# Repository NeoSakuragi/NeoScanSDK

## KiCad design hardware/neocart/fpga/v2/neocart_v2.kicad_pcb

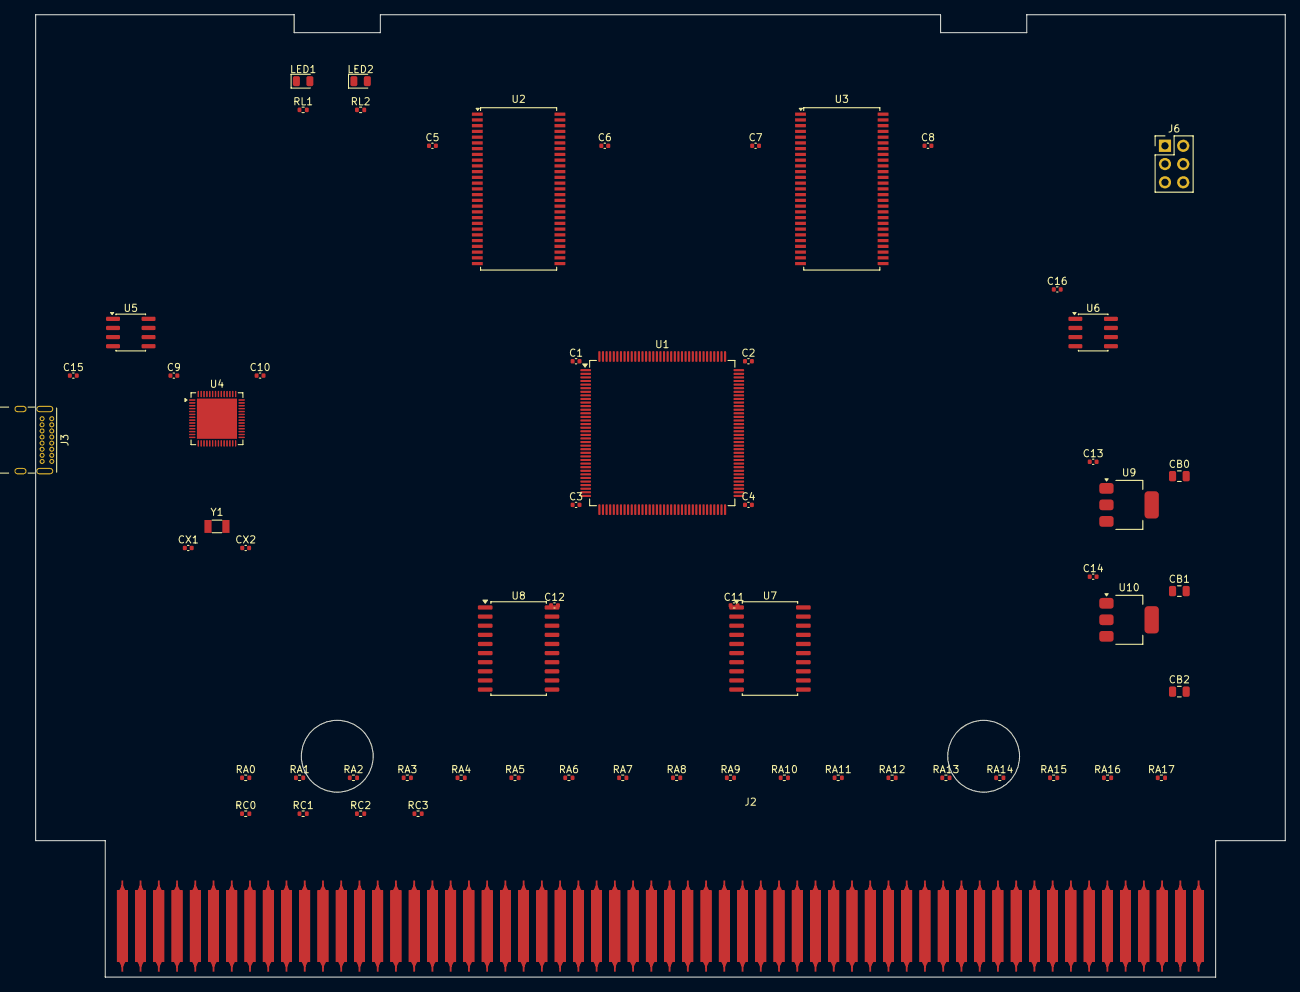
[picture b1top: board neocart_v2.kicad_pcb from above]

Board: 4 copper layers, 174.0 x 134.0 mm, 62 parts (0 on the bottom side), 102 nets, no tracks yet.

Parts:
C1, C2, C3, C4, C5, C6, C7, C8, C9, C10, C11, C12, C13, C14, C15, C16: 100n; C_0402_1005Metric
CB0, CB1, CB2: 10u; C_0805_2012Metric
CX1, CX2: 15p; C_0402_1005Metric
J1: CTRG2-B; neogeo-mvs-prog-b-side-edge
J2: CTRG2-A; neogeo-mvs-prog-a-side-edge
J3: USB; USB_C_Receptacle_GCT_USB4085
J6: JTAG; PinHeader_2x03_P2.54mm_Vertical
LED1: PWR; LED_0805_2012Metric
LED2: ACT; LED_0805_2012Metric
RA0, RA1, RA2, RA3, RA4, RA5, RA6, RA7, RA8, RA9, RA10, RA11, RA12, RA13, RA14, RA15, RA16, RA17: 470; R_0402_1005Metric
RC0, RC1, RC2, RC3: 470; R_0402_1005Metric
RL1, RL2: 1K; R_0402_1005Metric
U1: ECP5; TQFP-144_20x20mm_P0.5mm
U2: SDRAM1; TSOP-II-54_22.2x10.16mm_P0.8mm
U3: SDRAM2; TSOP-II-54_22.2x10.16mm_P0.8mm
U4: RP2040; QFN-56-1EP_7x7mm_P0.4mm_EP5.6x5.6mm
U5: FL-MCU; SOIC-8_3.9x4.9mm_P1.27mm
U6: FL-CFG; SOIC-8_3.9x4.9mm_P1.27mm
U7: 245-LO; SOIC-20W_7.5x12.8mm_P1.27mm
U8: 245-HI; SOIC-20W_7.5x12.8mm_P1.27mm
U9: 3V3; SOT-223-3_TabPin2
U10: 1V1; SOT-223-3_TabPin2
Y1: 12M; Crystal_SMD_3215-2Pin_3.2x1.5mm

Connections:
BUF_OE: U1.33, U7.19, U8.19
BUS_DIR: U1.31, U7.1, U8.1
FD0: U1.37, U7.18
FD1: U1.39, U7.17
FD2: U1.40, U7.16
FD3: U1.41, U7.15
FD4: U1.44, U7.14
FD5: U1.45, U7.13
FD6: U1.46, U7.12
FD7: U1.47, U7.11
FD8: U1.48, U8.18
FD9: U1.49, U8.17
FD10: U1.50, U8.16
FD11: U1.51, U8.15
FD12: U1.52, U8.14
FD13: U1.67, U8.13
FD14: U1.68, U8.12
FD15: U1.69, U8.11
GND: C1.2, C2.2, C3.2, C4.2, C5.2, C6.2, C7.2, C8.2, C9.2, C10.2, C11.2, C12.2, C13.2, C14.2, C15.2, C16.2, CB0.2, CB1.2, CB2.2, CX1.2, CX2.2, J1.1, J1.2, J1.3, J1.4, J1.59, J1.60, J2.1, J2.2, J2.3, J2.4, J2.59, J2.60, LED1.2, LED2.2, U1.15, U1.21, U1.36, U1.42, U1.54, U1.57, U1.60, U1.63, U1.66, U1.75, U1.87, U1.96, U1.123, U1.129, U1.132, U1.138, U1.144, U2.6, U2.12, U2.28, U2.40, U2.41, U2.46, U2.52, U2.54, U3.6, U3.12, U3.28, U3.40, U3.41, U3.46, U3.52, U3.54, U7.10, U8.10, U9.1, U10.1
LED1: LED1.1, RL1.1, RL1.2, U1.34
LED2: LED2.1, RL2.1, RL2.2, U1.35
PA0: J1.5, RA0.1, RA0.2, U1.1
PA1: J1.6, RA1.1, RA1.2, U1.2
PA2: J1.7, RA2.1, RA2.2, U1.3
PA3: J1.8, RA3.1, RA3.2, U1.4
PA4: J1.9, RA4.1, RA4.2, U1.5
PA5: J1.10, RA5.1, RA5.2, U1.6
PA6: J1.11, RA6.1, RA6.2, U1.7
PA7: J1.12, RA7.1, RA7.2, U1.10
PA8: J1.13, RA8.1, RA8.2, U1.11
PA9: J1.14, RA9.1, RA9.2, U1.12
PA10: J1.15, RA10.1, RA10.2, U1.13
PA11: J1.16, RA11.1, RA11.2, U1.14
PA12: J1.17, RA12.1, RA12.2, U1.18
PA13: J1.18, RA13.1, RA13.2, U1.19
PA14: J1.19, RA14.1, RA14.2, U1.22
PA15: J1.20, RA15.1, RA15.2, U1.23
PA16: J1.21, RA16.1, RA16.2, U1.24
PA17: J1.22, RA17.1, RA17.2, U1.25
PD0: J2.5, U7.2
PD1: J2.6, U7.3
PD2: J2.7, U7.4
PD3: J2.8, U7.5
PD4: J2.9, U7.6
PD5: J2.10, U7.7
PD6: J2.11, U7.8
PD7: J2.12, U7.9
PD8: J2.13, U8.2
PD9: J2.14, U8.3
PD10: J2.15, U8.4
PD11: J2.16, U8.5
PD12: J2.17, U8.6
PD13: J2.18, U8.7
PD14: J2.19, U8.8
PD15: J2.20, U8.9
ROMOE: J2.33, RC0.1, RC0.2, U1.26
ROMOEL: J2.24, RC2.1, RC2.2, U1.28
ROMOEU: J2.23, RC1.1, RC1.2, U1.27
SD_A0: U1.94, U2.23, U3.23
SD_A1: U1.95, U2.24, U3.24
SD_A2: U1.97, U2.25, U3.25
SD_A3: U1.98, U2.26, U3.26
SD_A4: U1.99, U2.29, U3.29
SD_A5: U1.102, U2.30, U3.30
SD_A6: U1.103, U2.31, U3.31
SD_A7: U1.104, U2.32, U3.32
SD_A8: U1.105, U2.33, U3.33
SD_A9: U1.106, U2.34, U3.34
SD_A10: U1.107, U2.22, U3.22
SD_A11: U1.108, U2.35, U3.35
SD_A12: U1.110, U2.36, U3.36
SD_BA0: U1.111, U2.20, U3.20
SD_BA1: U1.112, U2.21, U3.21
SD_CAS: U1.116, U2.17, U3.17
SD_CKE: U1.114, U2.37, U3.37
SD_CLK: U1.113, U2.38, U3.38
SD_CS0: U1.118, U2.19
SD_CS1: U1.119, U3.19
SD_DQ0: U1.73, U2.2, U3.2
SD_DQ1: U1.74, U2.4, U3.4
SD_DQ2: U1.76, U2.5, U3.5
SD_DQ3: U1.77, U2.7, U3.7
SD_DQ4: U1.78, U2.8, U3.8
SD_DQ5: U1.79, U2.10, U3.10
SD_DQ6: U1.80, U2.11, U3.11
SD_DQ7: U1.81, U2.13, U3.13
SD_DQ8: U1.82, U2.42, U3.42
SD_DQ9: U1.84, U2.44, U3.44
SD_DQ10: U1.88, U2.45, U3.45
SD_DQ11: U1.89, U2.47, U3.47
SD_DQ12: U1.90, U2.48, U3.48
SD_DQ13: U1.91, U2.50, U3.50
SD_DQ14: U1.92, U2.51, U3.51
SD_DQ15: U1.93, U2.53, U3.53
SD_DQMH: U1.121, U2.39, U3.39
SD_DQML: U1.120, U2.15, U3.15
SD_RAS: U1.115, U2.18, U3.18
SD_WE: U1.117, U2.16, U3.16
VCC_1V1: U1.16, U1.43, U1.55, U1.58, U1.61, U1.64, U1.70, U1.85, U1.100, U1.109, U1.130, U10.2
VCC_3V3: C1.1, C2.1, C3.1, C4.1, C5.1, C6.1, C7.1, C8.1, C9.1, C10.1, C11.1, C12.1, C13.1, C14.1, C15.1, C16.1, CB0.1, CB1.1, CB2.1, CX1.1, CX2.1, U1.8, U1.17, U1.20, U1.29, U1.32, U1.38, U1.53, U1.56, U1.59, U1.62, U1.65, U1.83, U1.86, U1.101, U1.122, U1.131, U1.137, U2.1, U2.3, U2.9, U2.14, U2.27, U2.43, U2.49, U3.1, U3.3, U3.9, U3.14, U3.27, U3.43, U3.49, U9.2, U10.3
VCC_5V: J1.29, J1.30, J1.31, J1.32, J2.29, J2.30, J2.31, J2.32, U7.20, U8.20, U9.3
nRW: J2.21, RC3.1, RC3.2, U1.30

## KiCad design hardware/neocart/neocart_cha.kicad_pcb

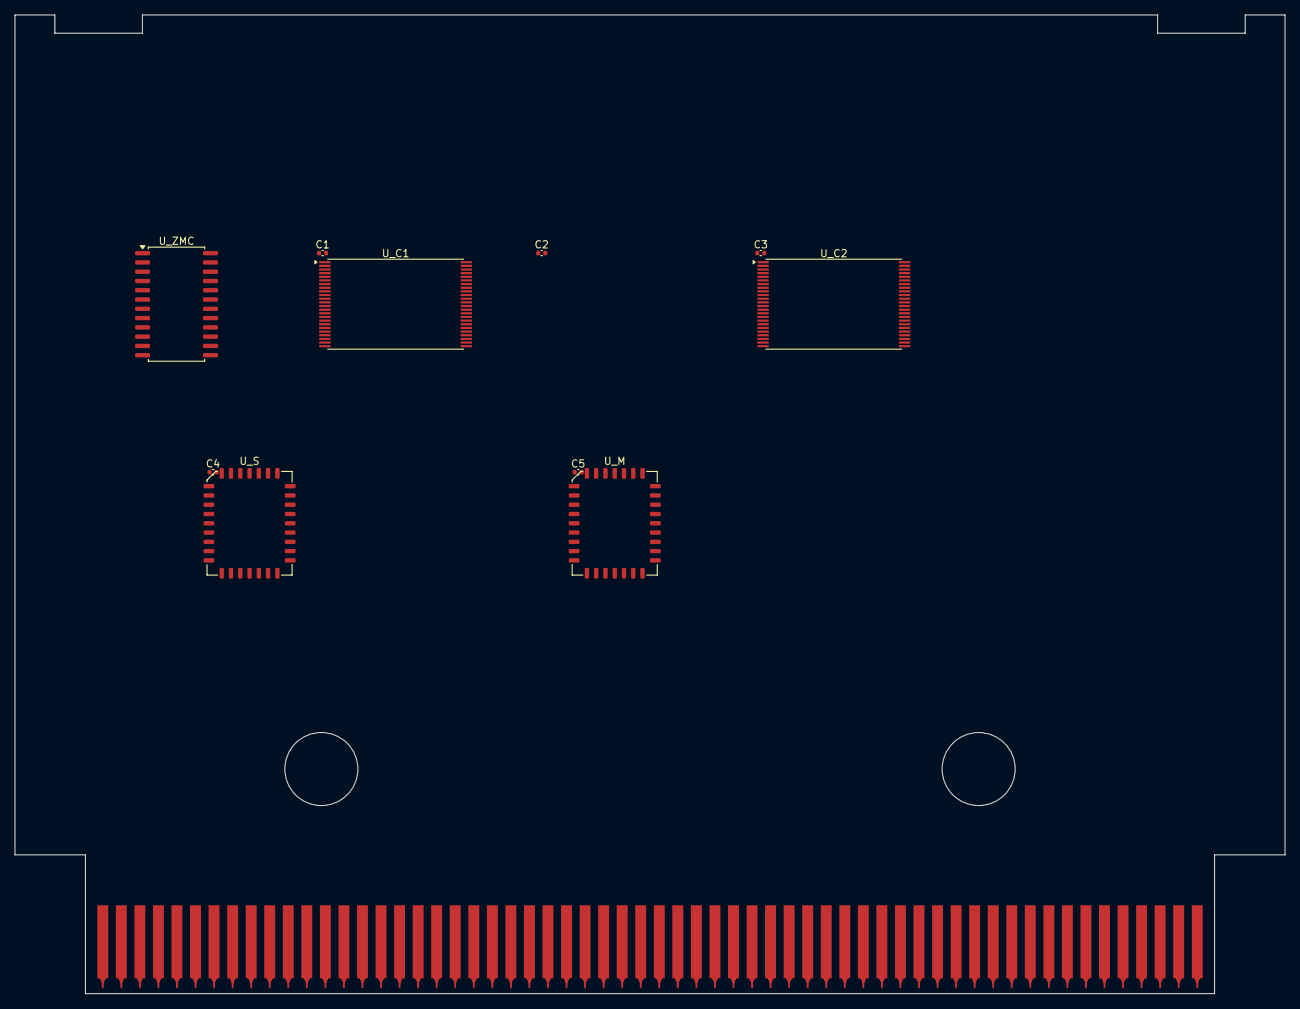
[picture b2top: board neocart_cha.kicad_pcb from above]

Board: 4 copper layers, 173.9 x 134.0 mm, 12 parts (1 on the bottom side), 2 nets, no tracks yet.

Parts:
C1, C2, C3, C4, C5: 100nF; C_0402_1005Metric
J1: neogeo-mvs-cha-a-side-edge; neogeo-mvs-a-side-edge
J4: neogeo-mvs-cha-b-side-edge; neogeo-mvs-b-side-edge
U_C1: AM29F400_C1; TSOP-I-48_18.4x12mm_P0.5mm
U_C2: AM29F400_C2; TSOP-I-48_18.4x12mm_P0.5mm
U_M: SST39SF010_M; PLCC-32_11.4x14.0mm_P1.27mm
U_S: SST39SF010_S; PLCC-32_11.4x14.0mm_P1.27mm
U_ZMC: NEO-ZMC; SOIC-24W_7.5x15.4mm_P1.27mm

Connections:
GND: J1.1 (GND), J1.2 (GND), J1.59 (GND), J1.60 (GND), J4.1 (GND), J4.2 (GND), J4.59 (GND), J4.60 (GND)
VCC: J1.29 (VCC), J1.30 (VCC), J1.31 (VCC), J1.32 (VCC), J4.29 (VCC), J4.30 (VCC), J4.31 (VCC), J4.32 (VCC)

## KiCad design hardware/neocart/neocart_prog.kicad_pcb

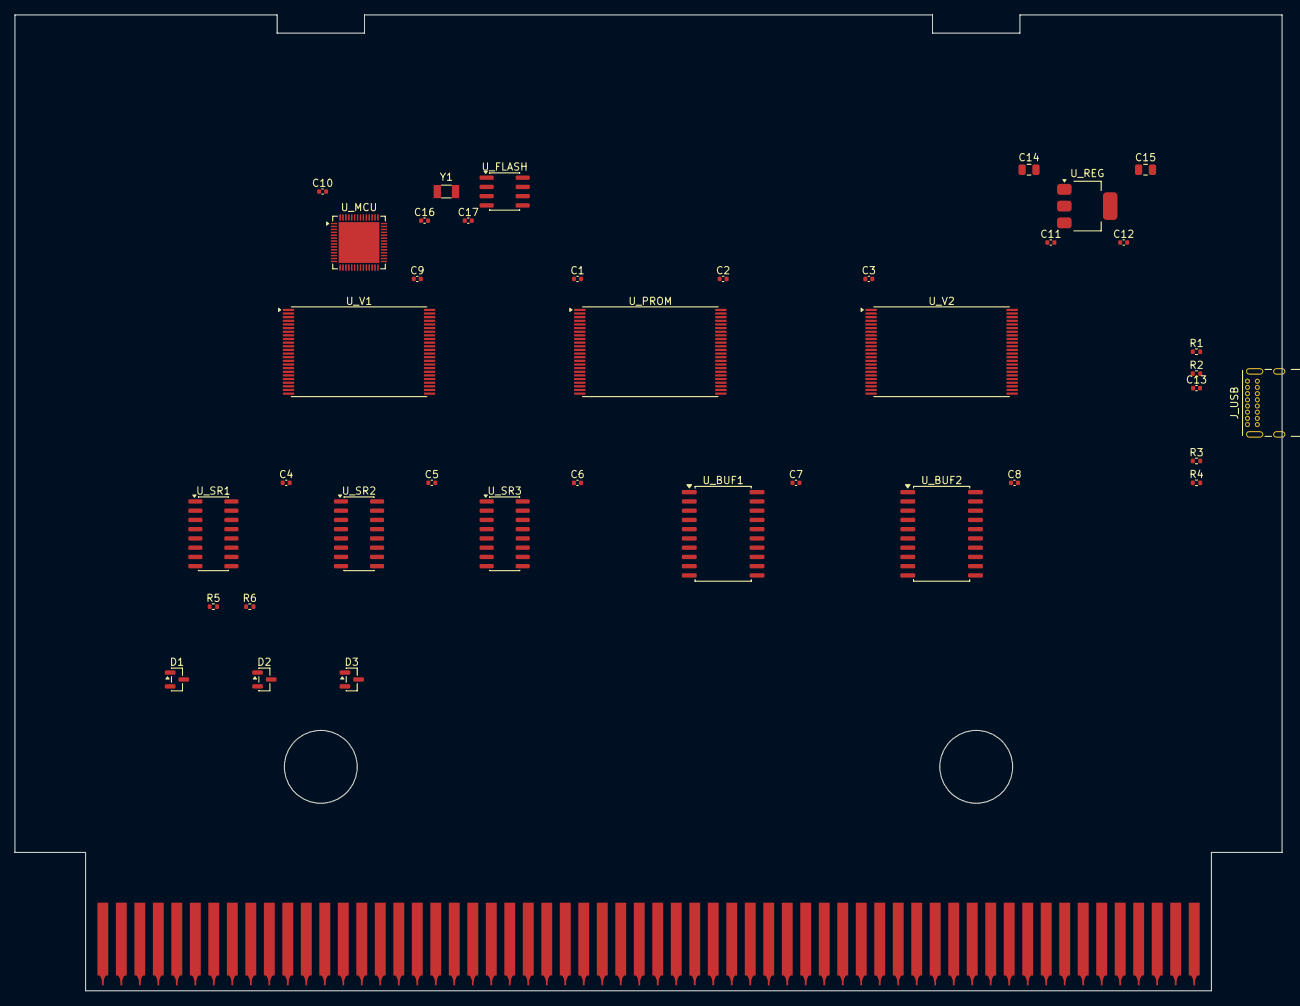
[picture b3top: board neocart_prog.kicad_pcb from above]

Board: 4 copper layers, 174.0 x 134.0 mm, 41 parts (1 on the bottom side), 2 nets, no tracks yet.

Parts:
C1, C2, C3, C4, C5, C6, C7, C8, C9, C10, C11, C12, C13: 100nF; C_0402_1005Metric
C14, C15: 10uF; C_0805_2012Metric
C16, C17: 15pF; C_0402_1005Metric
D1, D2, D3: BAT54S; SOT-23
J1: NeoGeo MVS Prog B Side Edge; neogeo-mvs-prog-b-side-edge
J2: NeoGeo MVS Prog A Side Edge; neogeo-mvs-prog-a-side-edge
J_USB: USB_C; USB_C_Receptacle_GCT_USB4085
R1, R2: 27R; R_0402_1005Metric
R3, R4: 5.1K; R_0402_1005Metric
R5, R6: 10K; R_0402_1005Metric
U_BUF1: 74HC245_DATA; SOIC-20W_7.5x12.8mm_P1.27mm
U_BUF2: 74HC245_CTRL; SOIC-20W_7.5x12.8mm_P1.27mm
U_FLASH: W25Q32; SOIC-8_3.9x4.9mm_P1.27mm
U_MCU: RP2040; QFN-56-1EP_7x7mm_P0.4mm_EP5.6x5.6mm
U_PROM: AM29F400_P; TSOP-I-48_18.4x12mm_P0.5mm
U_REG: AMS1117-3.3; SOT-223-3_TabPin2
U_SR1, U_SR2, U_SR3: 74HC595; SOIC-16_3.9x9.9mm_P1.27mm
U_V1: AM29F400_V1; TSOP-I-48_18.4x12mm_P0.5mm
U_V2: AM29F400_V2; TSOP-I-48_18.4x12mm_P0.5mm
Y1: 12MHz; Crystal_SMD_3215-2Pin_3.2x1.5mm

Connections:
GND: J1.1 (GND), J1.2 (GND), J1.3 (GND), J1.4 (GND), J1.57 (GND), J1.58 (GND), J1.59 (GND), J1.60 (GND), J2.1 (GND), J2.2 (GND), J2.3 (GND), J2.4 (GND), J2.57 (GND), J2.58 (GND), J2.59 (GND), J2.60 (GND)
VCC: J1.25 (ROMWAIT), J1.26 (PWAIT0), J1.27 (PWAIT1), J1.28 (PDTACK), J1.29 (VCC), J1.30 (VCC), J1.31 (VCC), J1.32 (VCC), J2.29 (VCC), J2.30 (VCC), J2.31 (VCC), J2.32 (VCC)

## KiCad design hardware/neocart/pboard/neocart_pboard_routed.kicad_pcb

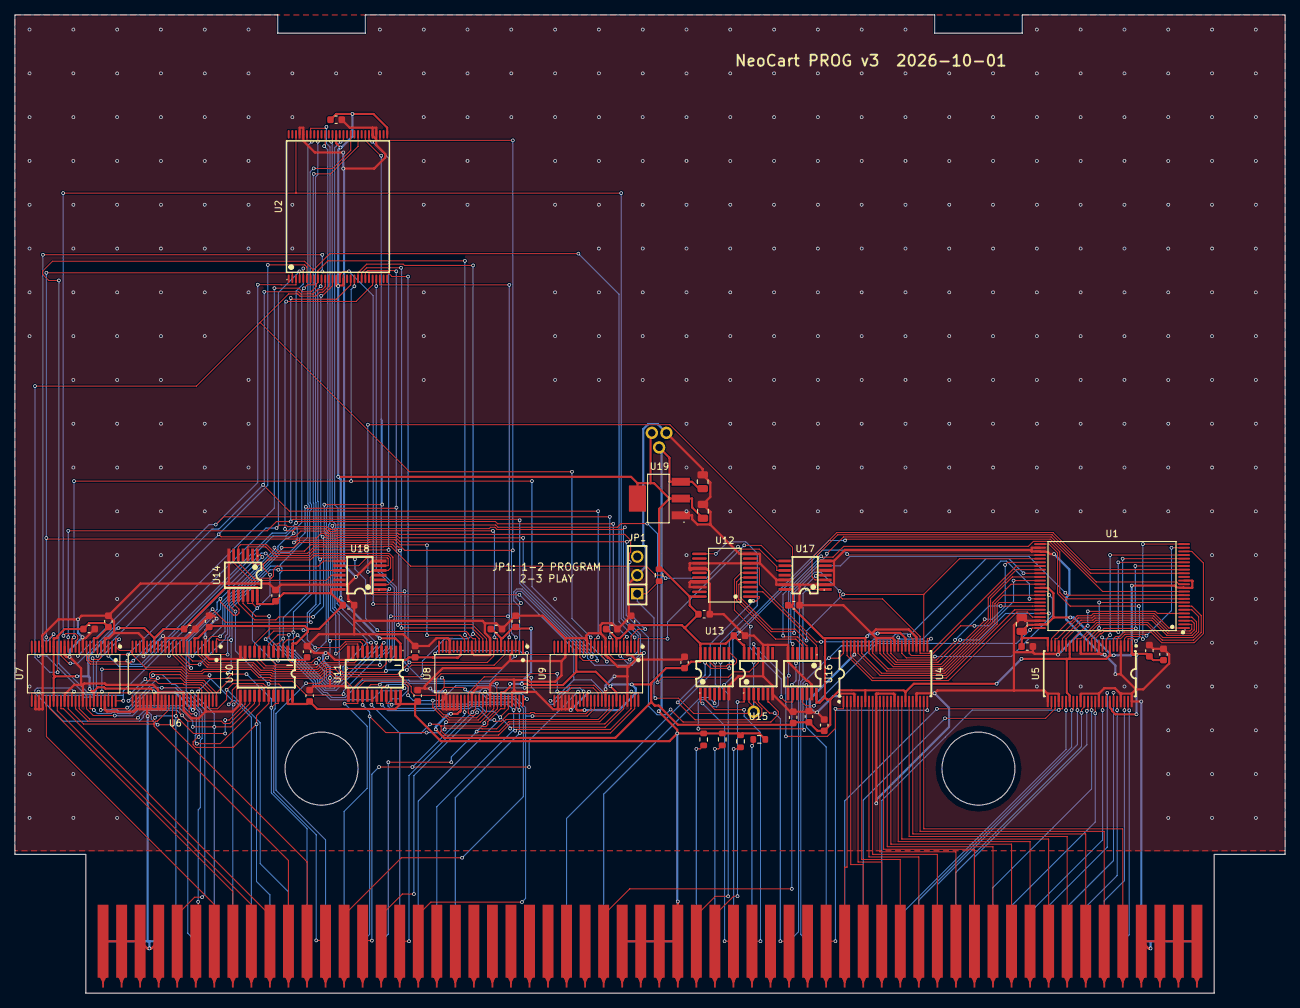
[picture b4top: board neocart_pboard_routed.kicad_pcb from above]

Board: 2 copper layers, 174.0 x 134.0 mm, 58 parts (1 on the bottom side), 172 nets.

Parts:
C1, C2, C3: 10u; C_0805_2012Metric
C4, C5, C6, C7, C8, C9, C10, C11, C12, C13, C14, C15, C16, C17, C18, C19, C20, C21, C22, C23, C24, C25, C26, C27, C28: 100n; C_0603_1608Metric
J1: NeoGeo MVS Prog B Side Edge; neogeo-mvs-prog-b-side-edge
J2: NeoGeo MVS Prog A Side Edge; neogeo-mvs-prog-a-side-edge
JP1: MODE; HDR-TH_03P-P2.54-V-M
R1, R2, R3, R4, R5: 10k; R_0603_1608Metric
TP1: GND; TP_PTH_1.0
TP2: P3V3; TP_PTH_1.0
TP3: VCC5; TP_PTH_1.0
TP4: nPROG; TP_PTH_1.0
U1: S29GL064N; TSOP-48_L12.0-W18.4-P0.50-LS20.0-BL
U2: S29GL128P; TSOP-56_L18.4-W14.0-P0.50-LS20.0-TL
U4, U5: SN74LVC16245A; TSSOP-48_L12.5-W6.1-P0.50-LS8.1-BL
U6, U7, U8, U9: 74LVC16374A; TSSOP-48_L12.6-W6.2-P0.50-LS8.1-BL
U10, U11: 74LVC8T245; TSSOP-24_L7.8-W4.4-P0.65-LS6.4-BL
U12: SN74AHC273; SSOP-20_L7.5-W5.2-P0.65-LS8.0-BL
U13, U14: SN74LVC08A; TSSOP-14_L5.0-W4.4-P0.65-LS6.4-BL
U15, U16, U17: 74LVC32A; TSSOP-14_L5.0-W4.4-P0.65-LS6.4-BL
U18: SN74LVC04A; TSSOP-14_L5.0-W4.4-P0.65-LS6.4-BL
U19: AMS1117-3.3; SOT-223-3_L6.5-W3.4-P2.30-LS7.0-BR

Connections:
A1: J1.5 (A1), U5.47
A2: J1.6 (A2), U5.46
A3: J1.7 (A3), U5.44
A4: J1.8 (A4), U5.43
A5: J1.9 (A5), U5.41
A6: J1.10 (A6), U5.40
A7: J1.11 (A7), U5.38
A8: J1.12 (A8), U5.37
A9: J1.13 (A9), U5.36
A10: J1.14 (A10), U5.35
A11: J1.15 (A11), U5.33
A12: J1.16 (A12), U5.32
A13: J1.17 (A13), U5.30
A14: J1.18 (A14), U5.29
A15: J1.19 (A15), U5.27
A16: J1.20 (A16), U5.26
A17: J1.21 (A17), U16.12
A18: J1.22 (A18), U17.1
A19: J1.23 (A19), U17.4
BANK0: U12.2, U16.1
BANK1: U12.5, U16.4
BANK2: U12.6, U16.9
D0: J2.5 (D0), U4.23
D1: J2.6 (D1), U4.22
D2: J2.7 (D2), U4.20
D3: J2.8 (D3), U4.19
D4: J2.9 (D4), U4.17
D5: J2.10 (D5), U4.16
D6: J2.11 (D6), U4.14
D7: J2.12 (D7), U4.13
D8: J2.13 (D8), U4.12
D9: J2.14 (D9), U4.11
D10: J2.15 (D10), U4.9
D11: J2.16 (D11), U4.8
D12: J2.17 (D12), U4.6
D13: J2.18 (D13), U4.5
D14: J2.19 (D14), U4.3
D15: J2.20 (D15), U4.2
FA0: U1.25, U5.2
FA1: U1.24, U5.3
FA2: U1.23, U5.5
FA3: U1.22, U5.6
FA4: U1.21, U5.8
FA5: U1.20, U5.9
FA6: U1.19, U5.11
FA7: U1.18, U5.12
FA8: U1.8, U5.13
FA9: U1.7, U5.14
FA10: U1.6, U5.16
FA11: U1.5, U5.17
FA12: U1.4, U5.19
FA13: U1.3, U5.20
FA14: U1.2, U5.22
FA15: U1.1, U5.23
FA16: U1.48, U16.11
FA17: U1.17, U17.3
FA18: U1.16, U17.6
FA19: U1.9, U16.3
FA20: U1.10, U16.6
FA21: U1.13, U16.8
FD0: U1.29, U4.26, U12.3
FD1: U1.31, U4.27, U12.4
FD2: U1.33, U4.29, U12.7
FD3: U1.35, U4.30
FD4: U1.38, U4.32
FD5: U1.40, U4.33
FD6: U1.42, U4.35
FD7: U1.44, U4.36
FD8: U1.30, U4.37
FD9: U1.32, U4.38
FD10: U1.34, U4.40
FD11: U1.36, U4.41
FD12: U1.39, U4.43
FD13: U1.41, U4.44
FD14: U1.43, U4.46
FD15: U1.45, U4.47
GND: C1.2, C2.2, C3.2, C4.2, C5.2, C6.2, C7.2, C8.2, C9.2, C10.2, C11.2, C12.2, C13.2, C14.2, C15.2, C16.2, C17.2, C18.2, C19.2, C20.2, C21.2, C22.2, C23.2, C24.2, C25.2, C26.2, C27.2, C28.2, J1.1 (GND), J1.2 (GND), J1.3 (GND), J1.4 (GND), J1.57 (GND), J1.58 (GND), J1.59 (GND), J1.60 (GND), J2.1 (GND), J2.2 (GND), J2.3 (GND), J2.4 (GND), J2.57 (GND), J2.58 (GND), J2.59 (GND), J2.60 (GND), JP1.2, TP1.1, U1.26, U1.27, U1.46, U2.32, U2.33, U2.52, U2.53, U4.4, U4.10, U4.15, U4.21, U4.28, U4.34, U4.39, U4.45, U5.4, U5.10, U5.15, U5.21, U5.25, U5.28, U5.34, U5.39, U5.45, U5.48, U6.4, U6.10, U6.15, U6.21, U6.26, U6.27, U6.28, U6.29, U6.30, U6.32, U6.33, U6.34, U6.39, U6.45, U7.4, U7.10, U7.15, U7.21, U7.26, U7.27, U7.28, U7.34, U7.39, U7.45, U8.4, U8.10, U8.15, U8.21, U8.26, U8.27, U8.28, U8.29, U8.30, U8.34, U8.39, U8.45, U9.4, U9.10, U9.15, U9.21, U9.26, U9.27, U9.28, U9.29, U9.30, U9.34, U9.39, U9.45, U10.11, U10.12, U10.13, U11.11, U11.12, U11.13, U12.8, U12.10, U12.13, U12.14, U12.17, U12.18, U13.7, U14.7, U15.7, U15.9, U15.10, U16.7, U16.13, U17.2, U17.5, U17.7, U17.12, U17.13, U18.7, U18.13, U19.1
P3V3: C2.1, C3.1, C4.1, C5.1, C6.1, C7.1, C8.1, C9.1, C10.1, C11.1, C12.1, C13.1, C14.1, C15.1, C16.1, C17.1, C18.1, C19.1, C20.1, C21.1, C22.1, C23.1, C24.1, C25.1, C27.1, R1.2, TP2.1, U1.12, U1.14, U1.37, U1.47, U2.14, U2.16, U2.29, U2.43, U4.7, U4.18, U4.31, U4.42, U5.1, U5.7, U5.18, U5.24, U5.31, U5.42, U6.7, U6.18, U6.31, U6.42, U7.7, U7.18, U7.31, U7.42, U8.7, U8.18, U8.31, U8.42, U9.7, U9.18, U9.31, U9.42, U10.1, U11.1, U11.2, U12.20, U13.14, U14.14, U15.14, U16.14, U17.14, U18.14, U19.2, U19.4
PDLY: U14.5, U17.10, U18.8
RW: J2.21 (R/W), U4.1, U4.24, U15.12
SDPA8: J2.43 (SDPA8), U8.36, U9.36
SDPA9: J2.44 (SDPA9), U8.35, U9.35
SDPA10: J2.45 (SDPA10), U8.33, U9.33
SDPA11: J2.46 (SDPA11), U8.32, U9.32
SDPAD0: J1.41 (SDPAD0), U8.47, U9.47, U11.21
SDPAD1: J1.42 (SDPAD1), U8.46, U9.46, U11.20
SDPAD2: J1.43 (SDPAD2), U8.44, U9.44, U11.19
SDPAD3: J1.44 (SDPAD3), U8.43, U9.43, U11.18
SDPAD4: J1.45 (SDPAD4), U8.41, U9.41, U11.17
SDPAD5: J1.46 (SDPAD5), U8.40, U9.40, U11.16
SDPAD6: J1.47 (SDPAD6), U8.38, U9.38, U11.15
SDPAD7: J1.48 (SDPAD7), U8.37, U9.37, U11.14
SDPMPX: J2.47 (SDPMPX), U8.25, U8.48, U18.3
SDPOE_I: U18.6, U18.9
SDRA8: J2.49 (SDRA8), U6.36, U7.36
SDRA9: J2.50 (SDRA9), U6.35, U7.35
SDRA20: J2.51 (SDRA20), U7.33
SDRA21: J2.52 (SDRA21), U7.32
SDRA22: J2.53 (SDRA22), U7.30
SDRA23: J2.54 (SDRA23), U7.29
SDRAD0: J1.49 (SDRAD0), U6.47, U7.47, U10.21
SDRAD1: J1.50 (SDRAD1), U6.46, U7.46, U10.20
SDRAD2: J1.51 (SDRAD2), U6.44, U7.44, U10.19
SDRAD3: J1.52 (SDRAD3), U6.43, U7.43, U10.18
SDRAD4: J1.53 (SDRAD4), U6.41, U7.41, U10.17
SDRAD5: J1.54 (SDRAD5), U6.40, U7.40, U10.16
SDRAD6: J1.55 (SDRAD6), U6.38, U7.38, U10.15
SDRAD7: J1.56 (SDRAD7), U6.37, U7.37, U10.14
SDRMPX: J2.55 (SDRMPX), U6.25, U6.48, U18.1
VCC5: C1.1, C26.1, C28.1, J1.29 (VCC), J1.30 (VCC), J1.31 (VCC), J1.32 (VCC), J2.29 (VCC), J2.30 (VCC), J2.31 (VCC), J2.32 (VCC), R2.2, R3.2, R4.2, R5.2, TP3.1, U10.23, U10.24, U11.23, U11.24, U19.3
VDIR: U10.2, U15.11
V_ADR0: U2.51, U6.2, U8.2
V_ADR1: U2.31, U6.3, U8.3
V_ADR2: U2.26, U6.5, U8.5
V_ADR3: U2.25, U6.6, U8.6
V_ADR4: U2.24, U6.8, U8.8
V_ADR5: U2.23, U6.9, U8.9
V_ADR6: U2.22, U6.11, U8.11
V_ADR7: U2.21, U6.12, U8.12
V_ADR8: U2.20, U6.13, U8.13
V_ADR9: U2.10, U6.14, U8.14
V_ADR10: U2.9, U7.2, U8.16
V_ADR11: U2.8, U7.3, U8.17
V_ADR12: U2.7, U7.5, U9.2
V_ADR13: U2.6, U7.6, U9.3
V_ADR14: U2.5, U7.8, U9.5
V_ADR15: U2.4, U7.9, U9.6
V_ADR16: U2.3, U7.11, U9.8
V_ADR17: U2.54, U7.12, U9.9
V_ADR18: U2.19, U7.13, U9.11
V_ADR19: U2.18, U7.14, U9.12
V_ADR20: U2.11, U7.16, U9.13
V_ADR21: U2.12, U7.17, U9.14
V_ADR22: U2.15, U7.19, U9.16
V_ADR23: U2.2, U7.20, U9.17
V_DQ0: U2.35, U10.3, U11.3
V_DQ1: U2.37, U10.4, U11.4
V_DQ2: U2.39, U10.5, U11.5
V_DQ3: U2.41, U10.6, U11.6
V_DQ4: U2.44, U10.7, U11.7
V_DQ5: U2.46, U10.8, U11.8
V_DQ6: U2.48, U10.9, U11.9
V_DQ7: U2.50, U10.10, U11.10
nASEL_OE: U6.1, U6.24, U7.1, U7.24, U18.10
nBSEL_OE: U8.1, U8.24, U9.1, U9.24, U17.8
nPDTACK: J1.28 (PDTACK), R5.1
nPMPX: U9.25, U9.48, U18.4
nPOE_BOTH: U14.6, U18.11
nPORTADRS: J2.33 (PORTADRS), U16.2, U16.5, U16.10
nPORTOE: U13.3, U13.5
nPORTOEL: J2.26 (PORTOEL), U13.1
nPORTOEU: J2.25 (PORTOEU), U13.2
nPORTWEL: J2.28 (PORTWEL), U12.11, U13.10
nPORTWEU: J2.27 (PORTWEU), U15.1
nPROG: JP1.1, R1.1, TP4.1, U15.2, U15.5, U15.13
nPWAIT0: J1.26 (PWAIT0), R3.1
nPWAIT1: J1.27 (PWAIT1), R4.1
nP_OE: U1.28, U13.6, U13.9
nP_WE: U1.11, U13.13, U15.3
nRESET: J1.35 (RESET), U12.1
nRMPX: U7.25, U7.48, U18.2
nROMOE: J1.33 (ROMOE), U13.4
nROMOEU: J2.23 (ROMOEU), U15.4
nROMWAIT: J1.25 (ROMWAIT), R2.1
nSDPOE: J2.48 (SDPOE), U14.2, U14.4, U14.12, U14.13, U17.9, U18.5
nSDROE: J2.56 (SDROE), U14.1, U14.9
nVA_BUFOE: U10.22, U14.8
nVB_BUFOE: U11.22, U14.11
nV_OE: U2.34, U14.3
nV_WE: U2.13, U14.10, U15.6
nXCVR_EN: U4.25, U4.48, U13.11
nXEN1: U13.8, U13.12

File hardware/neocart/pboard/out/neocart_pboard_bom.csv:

Comment,Designator,Footprint,LCSC Part #
100n,"C23,C5,C17,C15,C16,C26,C19,C22,C27,C8,C14,C21,C18,C28,C6,C4,C12,C9,C25,C7,C11,C20,C10,C24,C13",C0603,C14663
74LVC16245A,"U5,U4",TSSOP-48_L12.5-W6.1-P0.50-LS8.1-BL,C548160
74LVC8T245,"U11,U10",TSSOP-24_L7.8-W4.4-P0.65-LS6.4-BL,C458788
10k,"R3,R1,R5,R2,R4",R0603,C25804
74LVC08A,"U13,U14",TSSOP-14_L5.0-W4.4-P0.65-LS6.4-BL,C6053
74LVC32A,"U17,U16,U15",TSSOP-14_L5.0-W4.4-P0.65-LS6.4-BL,C6087
74LVC16374A,"U9,U8,U7,U6",TSSOP-48_L12.6-W6.2-P0.50-LS8.1-BL,C6074
10u,"C2,C3,C1",C0805,C15850
SN74AHC273,U12,SSOP-20_L7.5-W5.2-P0.65-LS8.0-BL,C2877489
S29GL064N,U1,TSOP-48_L12.0-W18.4-P0.50-LS20.0-BL,C117907
S29GL128P,U2,TSOP-56_L18.4-W14.0-P0.50-LS20.0-TL,C914939
SN74LVC04A,U18,TSSOP-14_L5.0-W4.4-P0.65-LS6.4-BL,C352968
AMS1117-3.3,U19,SOT-223-3_L6.5-W3.4-P2.30-LS7.0-BR,C6186

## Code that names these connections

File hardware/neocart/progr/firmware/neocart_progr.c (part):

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 * against the PROG board netlist (System.p_write, p_read, bank_write, ym_addr, v_read, v_write, power_on).
 *
 *   GPIO0-15   MD0-15     internal bus: U5 (D0-D15), U6 (SDRAD = MD0-7, SDPAD = MD8-15), latch inputs U10/U11
 *   GPIO26-40  strobes    RW nAS nROMOE nROMOEU nROMOEL nPORTOEU nPORTOEL nPORTWEU nPORTWEL nPORTADRS SDRMPX nSDROE SDPMPX nSDPOE CLK68K
 *   GPIO16-19  inputs     /ROMWAIT /PWAIT0 /PWAIT1 /PDTACK (cart outputs, 5 V tolerant pins, 1k series)
 *   GPIO20 XDIR (1 = programmer drives the cart)   21 /OE_D   22 /OE_VA   24 /OE_VB   41 /OE_OUT (strobes + latched lines)
 *   GPIO42 LCLK1 (A1-A16)   43 LCLK2 (A17-19, SDRA8/9/20-23, SDPA8-11, /RESET, 4 MHz, /SLOTCS)
 *   GPIO44 VCART_EN   45 /VCART_FAULT   46 VCART_SENSE (ADC6, 5 V -> 2.5 V)
 *   GPIO25 LED and GPIO23 KEY are on the WeAct module itself (KEY = start a flash of the last image, future use)
 *
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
